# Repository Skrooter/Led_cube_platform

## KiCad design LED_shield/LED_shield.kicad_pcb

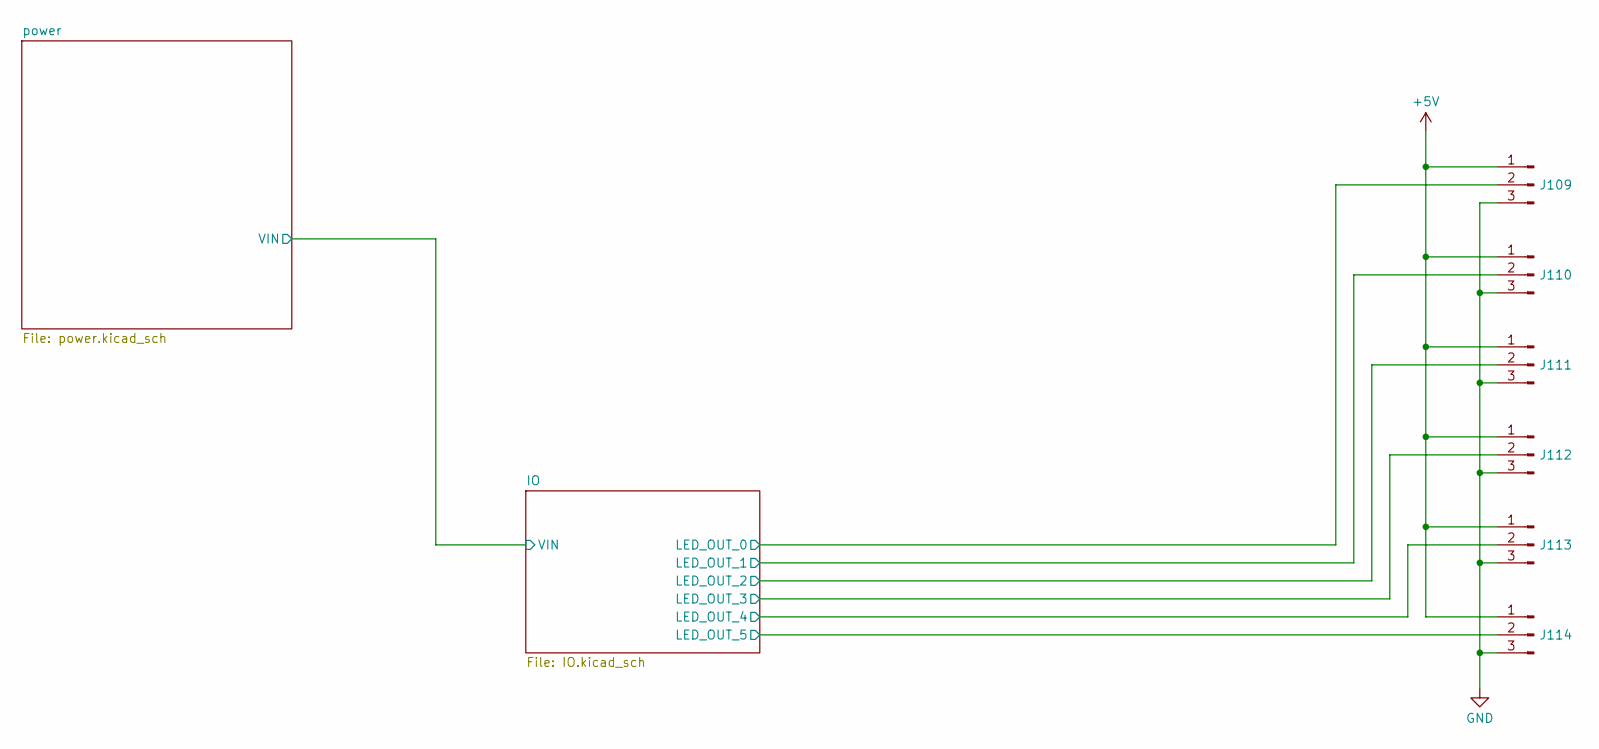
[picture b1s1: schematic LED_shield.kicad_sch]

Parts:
J109, J110, J111, J112, J113, J114: Screw_Terminal_01x03; PinHeader_1x03_P2.54mm_Vertical

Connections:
+5V: J109.1, J110.1, J111.1, J112.1, J113.1, J114.1; also elsewhere on the board
/IO/LED_OUT_0: J109.2; also elsewhere on the board
/IO/LED_OUT_1: J110.2; also elsewhere on the board
/IO/LED_OUT_2: J111.2; also elsewhere on the board
/IO/LED_OUT_3: J112.2; also elsewhere on the board
/IO/LED_OUT_4: J113.2; also elsewhere on the board
/IO/LED_OUT_5: J114.2; also elsewhere on the board
GND: J109.3, J110.3, J111.3, J112.3, J113.3, J114.3; also elsewhere on the board

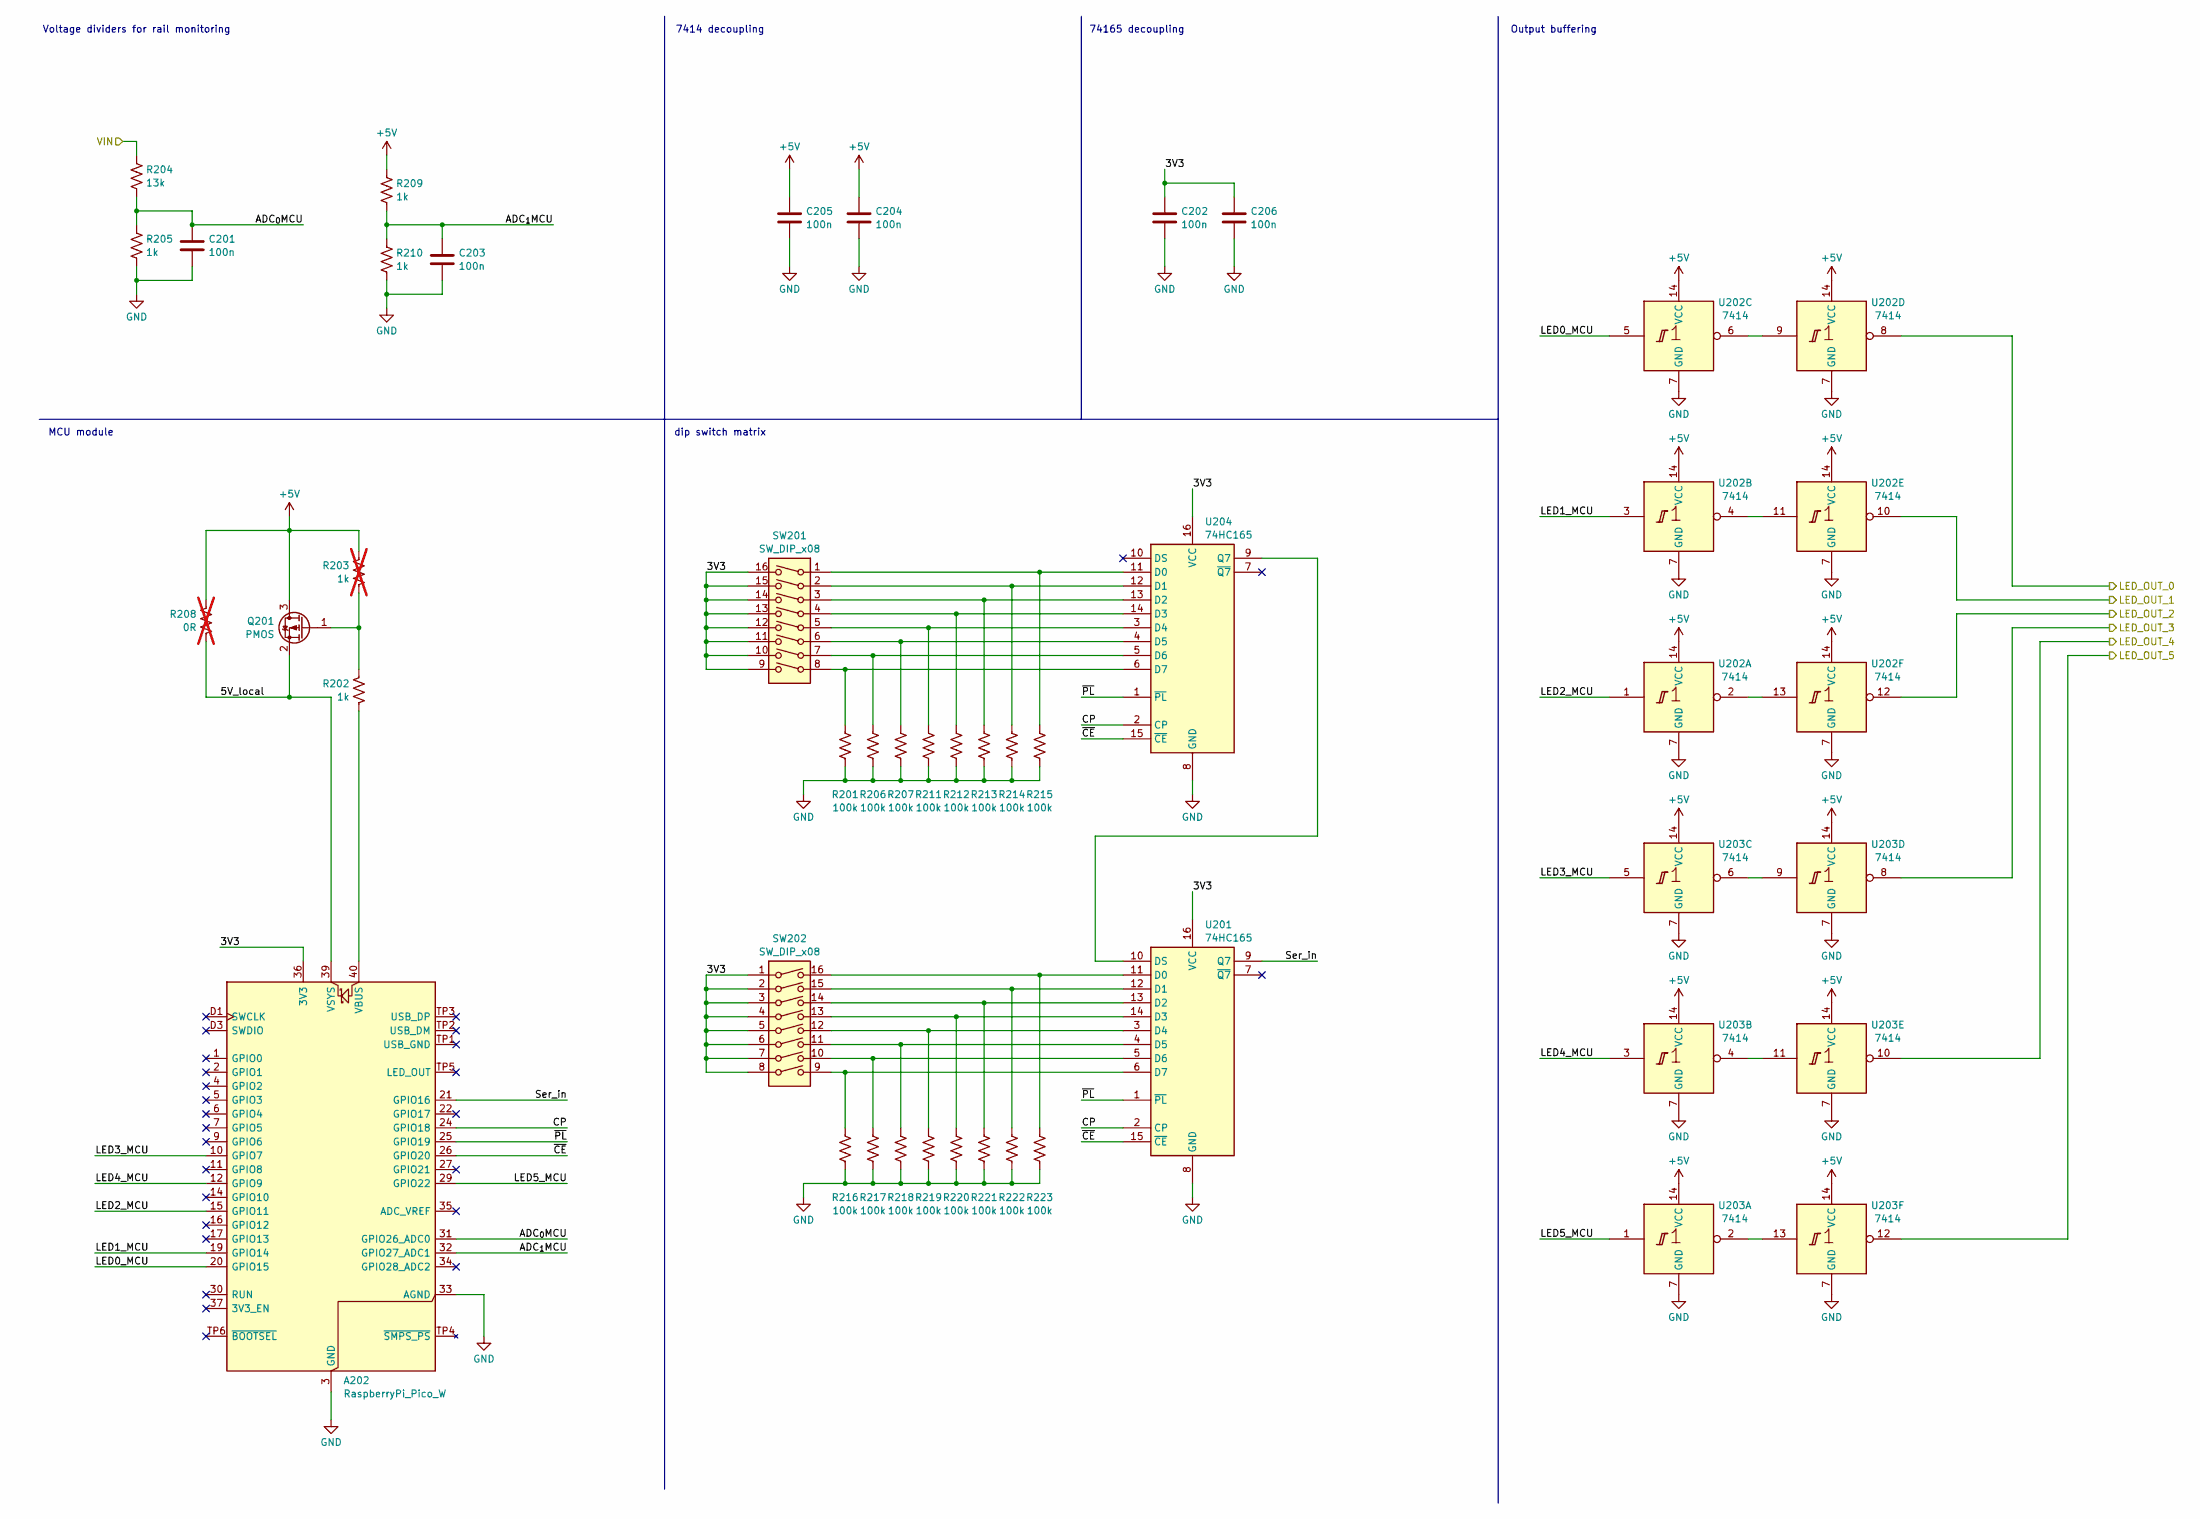
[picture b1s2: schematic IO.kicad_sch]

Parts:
A202: RaspberryPi_Pico_W; RaspberryPi_Pico_W_SMD
C201, C202, C203, C204, C205, C206: 100n; C_0402_1005Metric; LCSC C1525
Q201: PMOS; SOT-23; LCSC C10487
R201, R206, R207, R211, R212, R213, R214, R215, R216, R217, R218, R219, R220, R221, R222, R223: 100k; R_0402_1005Metric; LCSC C25741
R202, R205, R209, R210: 1k; R_0402_1005Metric; LCSC C11702
R203: 1k; R_0402_1005Metric; LCSC C11702; not fitted
R204: 13k; R_0603_1608Metric; LCSC C22797
R208: 0R; R_0402_1005Metric; LCSC C17168; not fitted
SW201, SW202: SW_DIP_x08; SW_DIP_SPSTx08_Slide_6.7x21.88mm_W8.61mm_P2.54mm_LowProfile; LCSC C5145023
U201, U204: 74HC165; SOIC-16_3.9x9.9mm_P1.27mm; LCSC C5613
U202, U203: 7414; SOIC-14_3.9x8.7mm_P1.27mm; LCSC C5605

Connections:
+5V: C204.1, C205.1, Q201.3 (D), R203.1, R208.1, R209.1, U202.14 (VCC), U203.14 (VCC); also elsewhere on the board
/IO/3V3: A202.36 (3V3), C202.1, C206.1, SW201.9, SW201.10, SW201.11, SW201.12, SW201.13, SW201.14, SW201.15, SW201.16, SW202.1, SW202.2, SW202.3, SW202.4, SW202.5, SW202.6, SW202.7, SW202.8, U201.16 (VCC), U204.16 (VCC)
/IO/5V_local: A202.39 (VSYS), Q201.2 (S), R208.2
/IO/ADC_{0}MCU: A202.31 (GPIO26_ADC0), C201.1, R204.2, R205.1
/IO/ADC_{1}MCU: A202.32 (GPIO27_ADC1), C203.1, R209.2, R210.1
/IO/CP: A202.24 (GPIO18), U201.2 (CP), U204.2 (CP)
/IO/LED0_MCU: A202.20 (GPIO15), U202.5
/IO/LED1_MCU: A202.19 (GPIO14), U202.3
/IO/LED2_MCU: A202.15 (GPIO11), U202.1
/IO/LED3_MCU: A202.10 (GPIO7), U203.5
/IO/LED4_MCU: A202.12 (GPIO9), U203.3
/IO/LED5_MCU: A202.29 (GPIO22), U203.1
/IO/LED_OUT_0: U202.8; also elsewhere on the board
/IO/LED_OUT_1: U202.10; also elsewhere on the board
/IO/LED_OUT_2: U202.12; also elsewhere on the board
/IO/LED_OUT_3: U203.8; also elsewhere on the board
/IO/LED_OUT_4: U203.10; also elsewhere on the board
/IO/LED_OUT_5: U203.12; also elsewhere on the board
/IO/Ser_in: A202.21 (GPIO16), U201.9 (Q7)
/IO/~CE: A202.26 (GPIO20), U201.15 (~CE), U204.15 (~CE)
/IO/~PL: A202.25 (GPIO19), U201.1 (~PL), U204.1 (~PL)
/power/VIN: R204.1; also elsewhere on the board
GND: A202.3 (GND), A202.8 (GND), A202.13 (GND), A202.18 (GND), A202.23 (GND), A202.28 (GND), A202.33 (AGND), A202.38 (GND), A202.D2 (GND), C201.2, C202.2, C203.2, C204.2, C205.2, C206.2, R201.2, R205.2, R206.2, R207.2, R210.2, R211.2, R212.2, R213.2, R214.2, R215.2, R216.2, R217.2, R218.2, R219.2, R220.2, R221.2, R222.2, R223.2, U201.8 (GND), U202.7 (GND), U203.7 (GND), U204.8 (GND); also elsewhere on the board
unnamed: A202.40 (VBUS), R202.1
unnamed: Q201.1 (G), R202.2, R203.2
unnamed: R223.1, SW202.16, U201.11 (D0)
unnamed: R222.1, SW202.15, U201.12 (D1)
unnamed: R221.1, SW202.14, U201.13 (D2)
unnamed: R220.1, SW202.13, U201.14 (D3)
unnamed: R219.1, SW202.12, U201.3 (D4)
unnamed: R218.1, SW202.11, U201.4 (D5)
unnamed: R217.1, SW202.10, U201.5 (D6)
unnamed: R216.1, SW202.9, U201.6 (D7)
unnamed: U201.10 (DS), U204.9 (Q7)
unnamed: U202.6, U202.9
unnamed: U202.4, U202.11
unnamed: U202.2, U202.13
unnamed: U203.6, U203.9
unnamed: U203.4, U203.11
unnamed: U203.2, U203.13
unnamed: R215.1, SW201.1, U204.11 (D0)
unnamed: R214.1, SW201.2, U204.12 (D1)
unnamed: R213.1, SW201.3, U204.13 (D2)
unnamed: R212.1, SW201.4, U204.14 (D3)
unnamed: R211.1, SW201.5, U204.3 (D4)
unnamed: R207.1, SW201.6, U204.4 (D5)
unnamed: R206.1, SW201.7, U204.5 (D6)
unnamed: R201.1, SW201.8, U204.6 (D7)

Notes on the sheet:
74165 decoupling
Output buffering
Voltage dividers for rail monitoring
MCU module
7414 decoupling
dip switch matrix

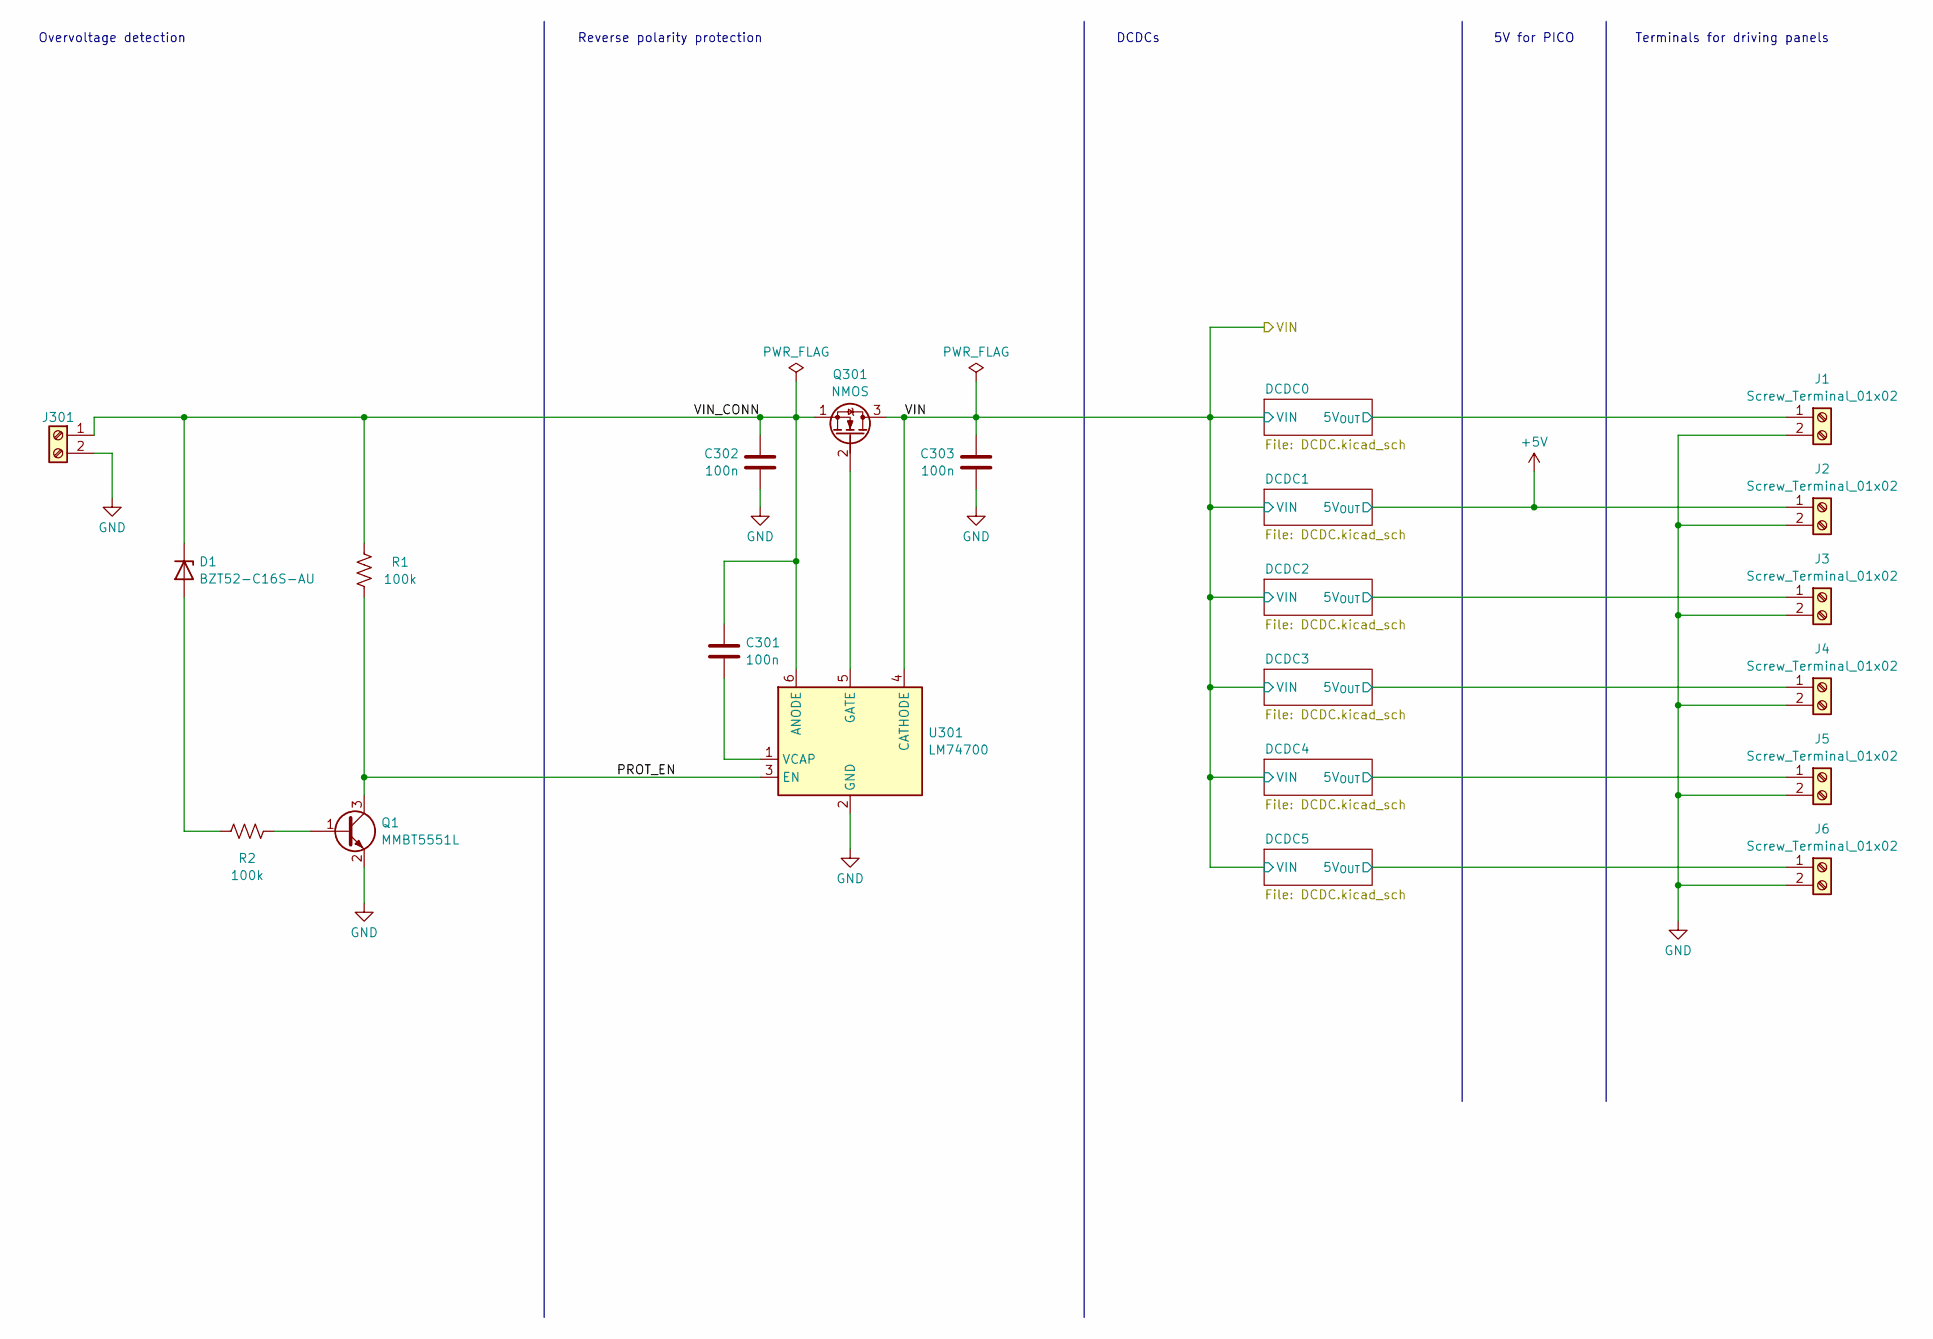
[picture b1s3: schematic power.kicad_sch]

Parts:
C301, C302, C303: 100n; C_0603_1608Metric; LCSC C14663
D1: BZT52-C16S-AU; D_SOD-323F; LCSC C393421
J1, J2, J3, J4, J5, J6: Screw_Terminal_01x02; PhoenixContact_MCV_1,5_2-G-3.81_1x02_P3.81mm_Vertical
J301: Screw_Terminal_01x02; PhoenixContact_MSTBVA_2,5_2-G-5,08_1x02_P5.08mm_Vertical
Q1: MMBT5551L; SOT-23; LCSC C2145
Q301: NMOS; VSONP-8-1EP_5x6_P1.27mm; LCSC C2683366
R1, R2: 100k; R_0402_1005Metric; LCSC C25741
U301: LM74700; SOT-23-6; LCSC C2941042

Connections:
+5V: J2.1; also elsewhere on the board
/power/DCDC0/5V_{OUT}: J1.1; also elsewhere on the board
/power/DCDC2/5V_{OUT}: J3.1; also elsewhere on the board
/power/DCDC3/5V_{OUT}: J4.1; also elsewhere on the board
/power/DCDC4/5V_{OUT}: J5.1; also elsewhere on the board
/power/DCDC5/5V_{OUT}: J6.1; also elsewhere on the board
/power/PROT_EN: Q1.3 (C), R1.2, U301.3 (EN)
/power/VIN: C303.2, Q301.3 (D), U301.4 (CATHODE); also elsewhere on the board
/power/VIN_CONN: C301.1, C302.2, D1.1 (K), J301.1, Q301.1 (S), R1.1, U301.6 (ANODE)
GND: C302.1, C303.1, J1.2, J2.2, J3.2, J4.2, J5.2, J6.2, J301.2, Q1.2 (E), U301.2 (GND); also elsewhere on the board
unnamed: D1.2 (A), R2.1
unnamed: Q1.1 (B), R2.2
unnamed: Q301.2 (G), U301.5 (GATE)
unnamed: C301.2, U301.1 (VCAP)

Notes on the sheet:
Reverse polarity protection
Terminals for driving panels
Overvoltage detection
DCDCs
5V for PICO

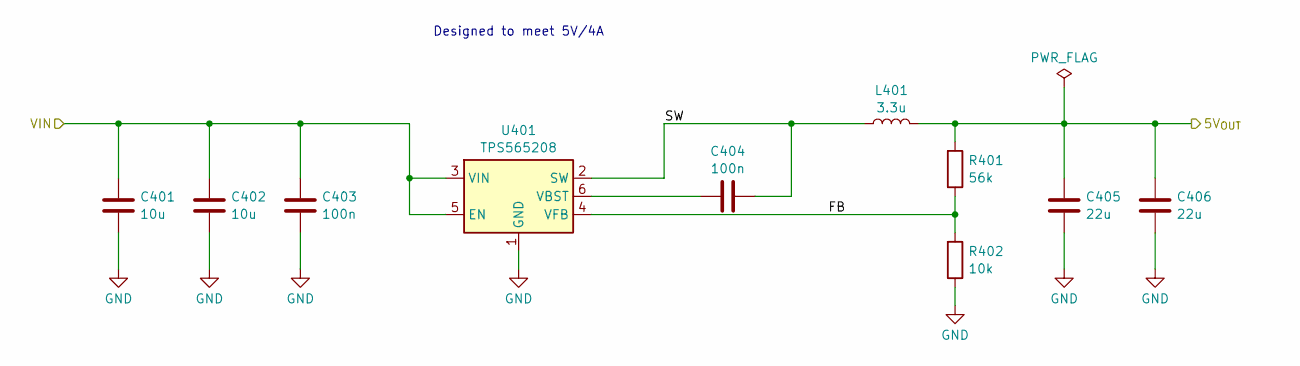
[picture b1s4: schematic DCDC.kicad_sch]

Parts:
C401, C402: 10u; C_0805_2012Metric; LCSC C440198
C403: 100n; C_0603_1608Metric; LCSC C14663
C404: 100n; C_0402_1005Metric; LCSC C1525
C405, C406: 22u; C_0805_2012Metric; LCSC C45783
L401: 3.3u; IHLP3232; LCSC C511015
R401: 56k; R_0603_1608Metric; LCSC C23206
R402: 10k; R_0603_1608Metric; LCSC C25197
U401: TPS565208; SOT-23-6; LCSC C2650336

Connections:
/power/DCDC0/5V_{OUT}: C405.1, C406.1, L401.2, R401.2; also elsewhere on the board
/power/DCDC0/FB: R401.1, R402.2, U401.4 (VFB)
/power/DCDC0/SW: C404.2, L401.1, U401.2 (SW)
/power/VIN: C401.1, C402.1, C403.2, U401.3 (VIN), U401.5 (EN); also elsewhere on the board
GND: C401.2, C402.2, C403.1, C405.2, C406.2, R402.1, U401.1 (GND); also elsewhere on the board
unnamed: C404.1, U401.6 (VBST)

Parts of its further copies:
C501, C502, C601, C602, C701, C702, C801, C802, C901, C902: 10u; C_0805_2012Metric; LCSC C440198
C503, C603, C703, C803, C903: 100n; C_0603_1608Metric; LCSC C14663
C504, C604, C704, C804, C904: 100n; C_0402_1005Metric; LCSC C1525
C505, C506, C605, C606, C705, C706, C805, C806, C905, C906: 22u; C_0805_2012Metric; LCSC C45783
L501, L601, L701, L801, L901: 3.3u; IHLP3232; LCSC C511015
R501, R601, R701, R801, R901: 56k; R_0603_1608Metric; LCSC C23206
R502, R602, R702, R802, R902: 10k; R_0603_1608Metric; LCSC C25197
U501, U601, U701, U801, U901: TPS565208; SOT-23-6; LCSC C2650336

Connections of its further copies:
+5V: C505.1, C506.1, L501.2, R501.2; also elsewhere on the board
/power/DCDC1/FB: R501.1, R502.2, U501.4 (VFB)
/power/DCDC1/SW: C504.2, L501.1, U501.2 (SW)
/power/DCDC2/5V_{OUT}: C605.1, C606.1, L601.2, R601.2; also elsewhere on the board
/power/DCDC2/FB: R601.1, R602.2, U601.4 (VFB)
/power/DCDC2/SW: C604.2, L601.1, U601.2 (SW)
/power/DCDC3/5V_{OUT}: C705.1, C706.1, L701.2, R701.2; also elsewhere on the board
/power/DCDC3/FB: R701.1, R702.2, U701.4 (VFB)
/power/DCDC3/SW: C704.2, L701.1, U701.2 (SW)
/power/DCDC4/5V_{OUT}: C805.1, C806.1, L801.2, R801.2; also elsewhere on the board
/power/DCDC4/FB: R801.1, R802.2, U801.4 (VFB)
/power/DCDC4/SW: C804.2, L801.1, U801.2 (SW)
/power/DCDC5/5V_{OUT}: C905.1, C906.1, L901.2, R901.2; also elsewhere on the board
/power/DCDC5/FB: R901.1, R902.2, U901.4 (VFB)
/power/DCDC5/SW: C904.2, L901.1, U901.2 (SW)
/power/VIN: C501.1, C502.1, C503.2, C601.1, C602.1, C603.2, C701.1, C702.1, C703.2, C801.1, C802.1, C803.2, C901.1, C902.1, C903.2, U501.3 (VIN), U501.5 (EN), U601.3 (VIN), U601.5 (EN), U701.3 (VIN), U701.5 (EN), U801.3 (VIN), U801.5 (EN), U901.3 (VIN), U901.5 (EN); also elsewhere on the board
GND: C501.2, C502.2, C503.1, C505.2, C506.2, C601.2, C602.2, C603.1, C605.2, C606.2, C701.2, C702.2, C703.1, C705.2, C706.2, C801.2, C802.2, C803.1, C805.2, C806.2, C901.2, C902.2, C903.1, C905.2, C906.2, R502.1, R602.1, R702.1, R802.1, R902.1, U501.1 (GND), U601.1 (GND), U701.1 (GND), U801.1 (GND), U901.1 (GND); also elsewhere on the board
unnamed: C504.1, U501.6 (VBST)
unnamed: C604.1, U601.6 (VBST)
unnamed: C704.1, U701.6 (VBST)
unnamed: C804.1, U801.6 (VBST)
unnamed: C904.1, U901.6 (VBST)

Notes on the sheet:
Designed to meet 5V/4A

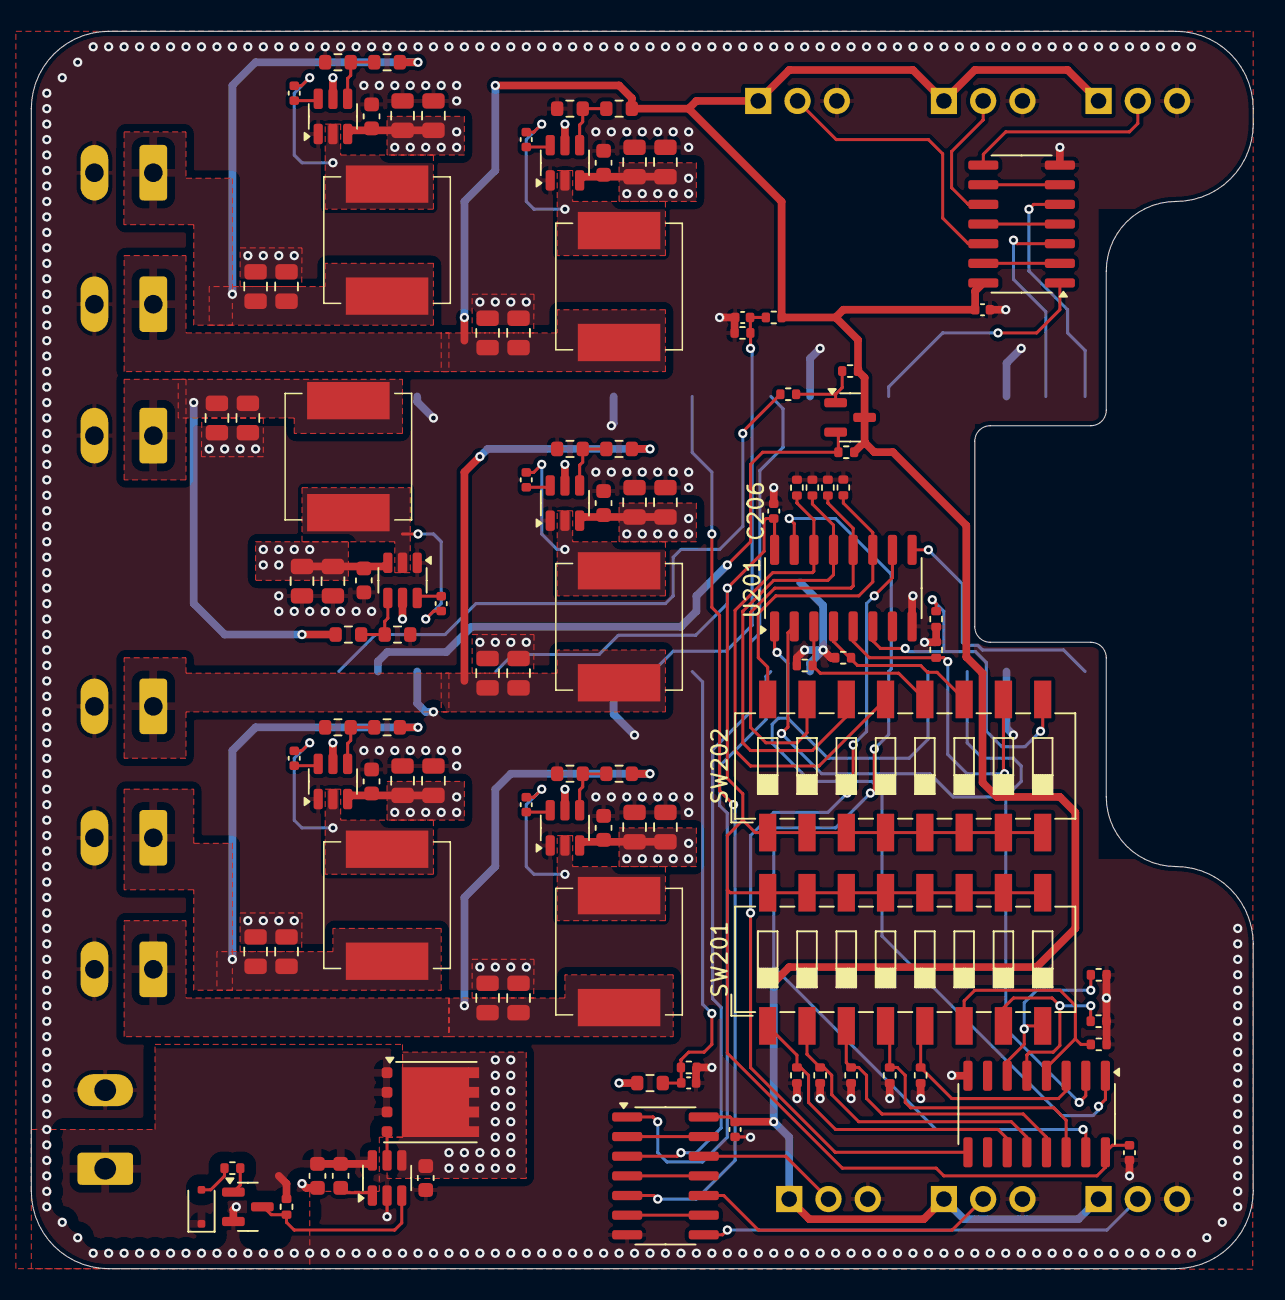
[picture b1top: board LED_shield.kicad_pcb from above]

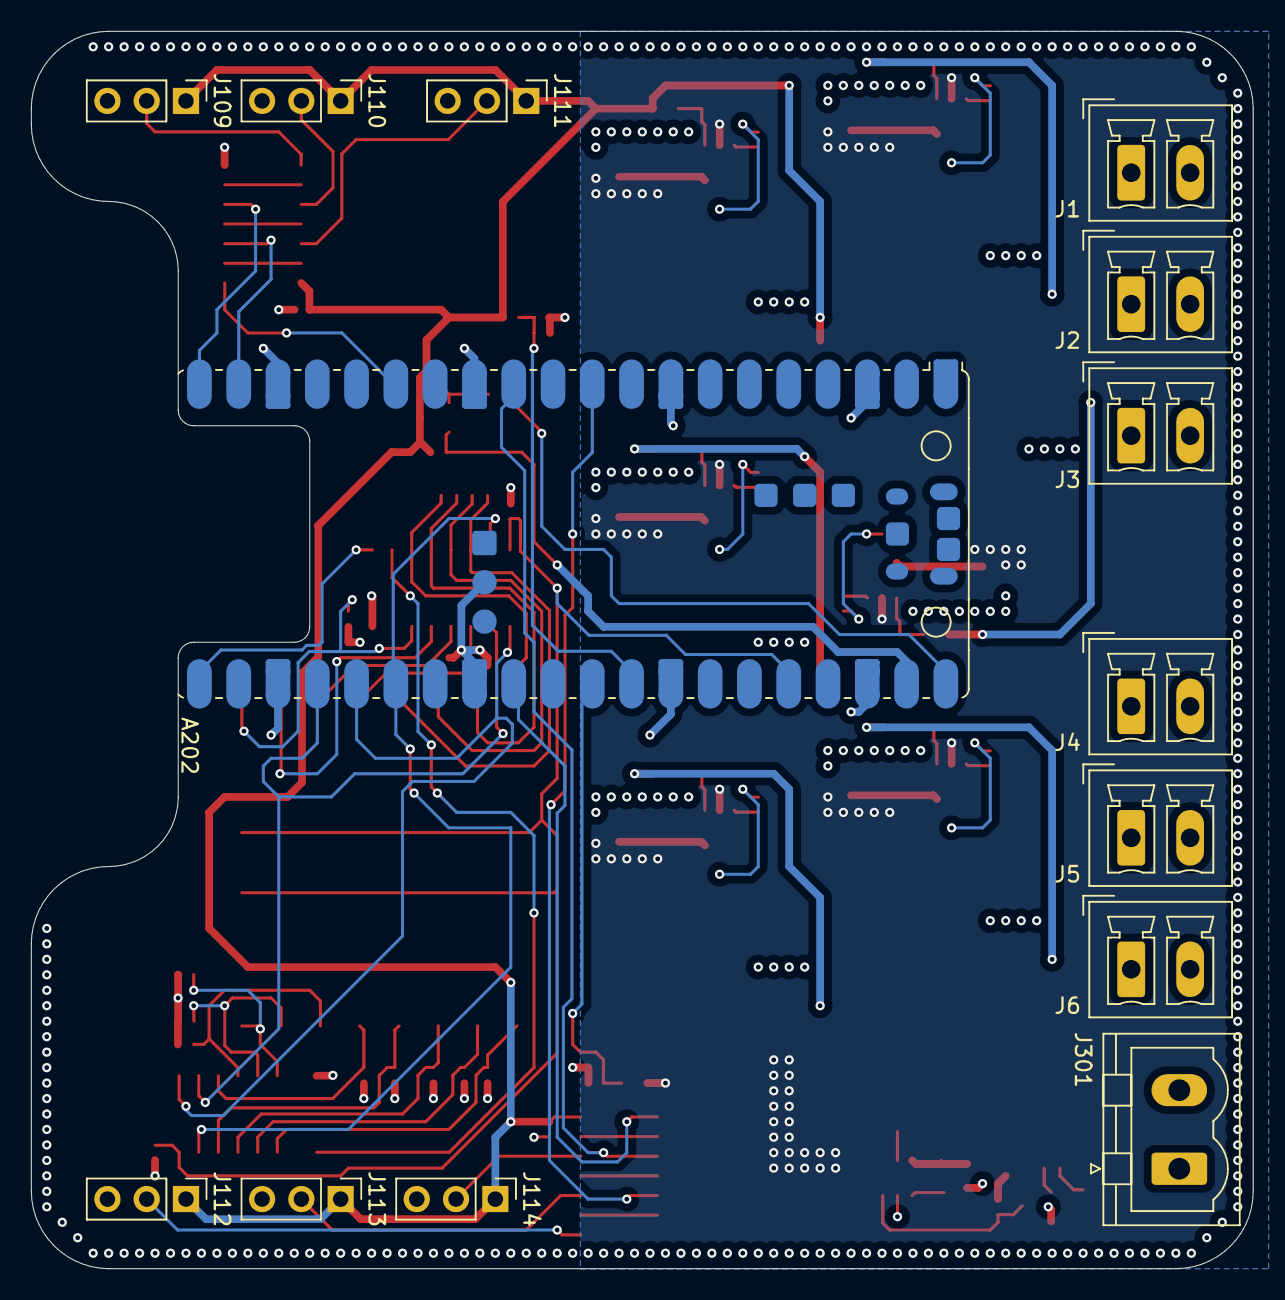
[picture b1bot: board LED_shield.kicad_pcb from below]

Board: 4 copper layers, 79.0 x 80.0 mm, 119 parts (14 on the bottom side), 77 nets.

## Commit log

2024-07-10 Inital schematic commit
2024-07-15 Finish most of PCB design
2024-07-17 Remove unused components
2024-07-22 Small fixes before production
2024-07-22 Small schematic change
2024-08-07 Make PCB ready for manufacture (again)
2024-08-07 Remove temp files and sync project
2024-08-07 Add missing LCSC partnumbers
    Also fixed grouping in PCB
2024-08-07 Fix DRC issue in PCB
